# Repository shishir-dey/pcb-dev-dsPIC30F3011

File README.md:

# pcb-dev-dsPIC30F3011

<h3>Front View (3D)</h3>

<h3>Bare PCB</h3>

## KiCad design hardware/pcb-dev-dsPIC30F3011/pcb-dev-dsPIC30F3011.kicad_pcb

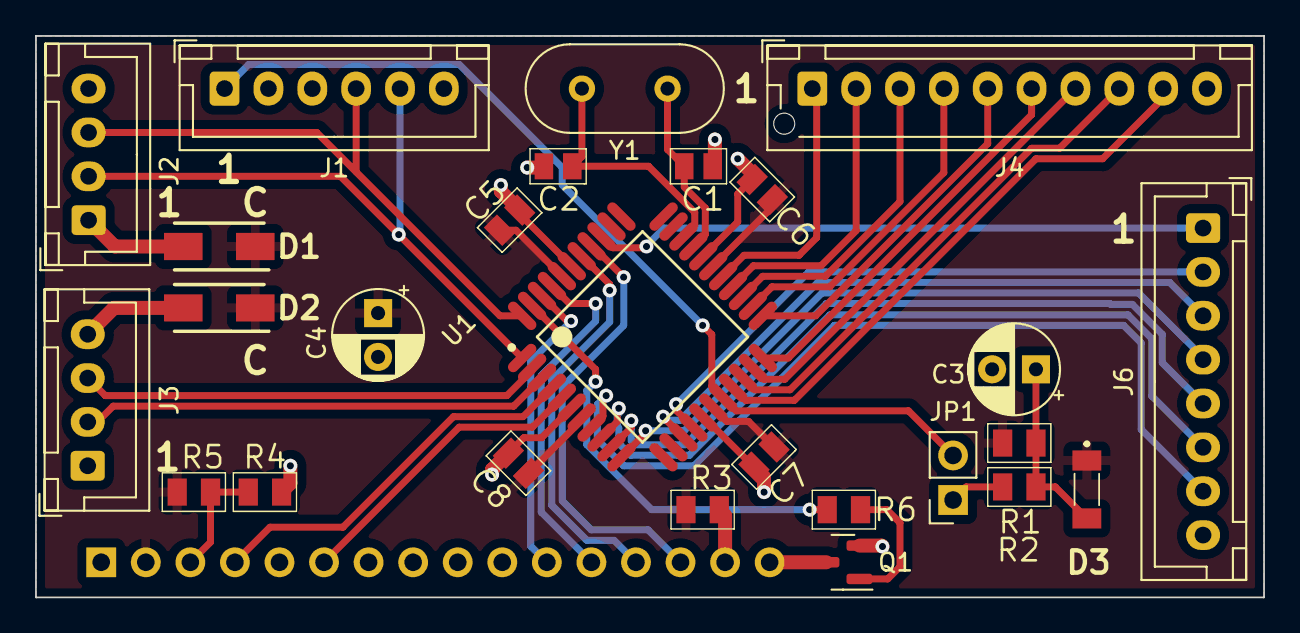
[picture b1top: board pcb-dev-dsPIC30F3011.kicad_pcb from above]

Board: 2 copper layers, 70.0 x 32.0 mm, 27 parts (1 on the bottom side), 40 nets.

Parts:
C1, C2: 22pf, 0805; CAPC2012X90N
C3: 2.2uF, 25V; CP_Radial_D5.0mm_P2.50mm
C4: 10nF, 63V; CP_Radial_D5.0mm_P2.50mm
C5, C6, C7, C8: 104, 0805; CAPC2012X90N
D1, D2: D; DIOM5127X229N
D3: CLL4148; FDLL4448
J1: Conn_PIC_ICSP_ICD; JST_XH_B6B-XH-A_1x06_P2.50mm_Vertical
J2, J3: 4 pin JST 2.54; JST_XH_B4B-XH-A_1x04_P2.50mm_Vertical
J4: 10 pin JST 2.54; JST_XH_B10B-XH-AM_1x10_P2.50mm_Vertical
J5: 16 pin header 2.54; PinSocket_1x16_P2.54mm_Vertical
J6: 8 pin JST 2.54; JST_XH_B8B-XH-A_1x08_P2.50mm_Vertical
JP1: Jumper; PinSocket_1x02_P2.54mm_Vertical
Q1: BC847, SOT-23; SOT-23
R1: 22K,0805; RESC2012X60N
R2: 470E,0805; RESC2012X60N
R3: SHORT; RESC2012X60N
R4: 1K; RESC2012X60N
R5: 9.1K; RESC2012X60N
R6: 22E; RESC2012X60N
U1: DSPIC30F3011-30I_PT; Microchip-DSPIC30F3011-30I_PT-Level_A
Y1: Crystal; Crystal_HC49-U_Vertical

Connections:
+5V: C4.1, C5.1, C6.1, C7.1, C8.1, D1.1 (K), D2.1 (K), D3.1 (K), J5.2, R1.1, R3.1, R5.2, U1.7 (VDD), U1.17 (AVDD), U1.28 (VDD), U1.40 (VDD)
ADC0: J4.9, U1.19 (EMUD3/AN0/VREF+/CN2/RB0)
ADC1: J4.8, U1.20 (EMUC3/AN1/VREF-/CN3/RB1)
ADC2: J4.7, U1.21 (~SS1/CN4RB2)
ADC3: J4.6, U1.22 (AN3/INDX/CN5/RB3)
ADC4: J4.5, U1.23 (AN4/QEA/IC7/CN6/RB4)
ADC5: J4.4, U1.24 (AN5/QEB/IC8/CN7/RB5)
ADC6: J4.3, U1.25 (AN6/OCFA/RB6)
ADC7: J4.2, U1.26 (AN7/RB7)
ADC8: J4.1, U1.27 (AN8/RB8)
CLKIN: C1.1, U1.30 (OSC1/CLKI), Y1.1
CLKOUT: C2.1, U1.31 (OSC2/CLKO/RC15), Y1.2
FAULT: J6.1, U1.36 (~FLTA/INT0RE8)
GND: C1.2, C2.2, C3.2, C4.2, C5.2, C6.2, C7.2, C8.2, J1.3 (VSS), J2.4, J3.1, J4.10, J5.1, J5.5, J5.7, J5.8, J5.9, J5.10, J6.8, Q1.2 (E), R4.1, U1.6 (VSS), U1.16 (AVSS), U1.29 (VSS), U1.39 (VSS)
LCD_BACKLIGHT: R6.1, U1.43 (SCK1/RF6)
LCD_CS_RS: J5.4, U1.4 (RF1)
LCD_DATA0: J5.11, U1.42 (EMUC2/OC1/IC1/INT1/RD0)
LCD_DATA1: J5.12, U1.41 (OC3/RD2)
LCD_DATA2: J5.13, U1.38 (OC4/RD3)
LCD_DATA3: J5.14, U1.37 (EMUD2/OC2/IC2/INT2/RD1)
LCD_WR_ENABLE: J5.6, U1.5 (RF0)
unnamed: C3.1, D3.2 (A), R1.2, R2.2
unnamed: J5.3, R4.2, R5.1
unnamed: J5.15, R3.2
unnamed: J5.16, Q1.3 (C)
unnamed: JP1.1 (A), R2.1
unnamed: Q1.1 (B), R6.2
PICkit4_MCLR: J1.1 (~MCLR/VPP), JP1.2 (B), U1.18 (~MCLR)
PICkit4_PGC: J1.5 (PGC/ICSPCLK), J2.2, U1.1 (PGC/EMUC/U1RX/SDI1/SDA/RF2)
PICkit4_PGD: J1.4 (PGD/ICSPDAT), J2.3, U1.44 (PGD/EMUD/U1TX/SDO1/SCL/RF3)
PWM1H: J6.3, U1.14 (PWM1H/RE1)
PWM1L: J6.2, U1.15 (PWM1L/RE0)
PWM2H: J6.5, U1.10 (PWM2H/RE3)
PWM2L: J6.4, U1.11 (PWM2L/RE2)
PWM3H: J6.7, U1.8 (PWM3H/RE5)
PWM3L: J6.6, U1.9 (PWM3L/RE4)
UART1_+5V: D1.2 (A), J2.1
UART2_+5V: D2.2 (A), J3.4
UART2_RX: J3.2, U1.3 (U2RX/CN17/RF4)
UART2_TX: J3.3, U1.2 (U2TX/CN18/RF5)

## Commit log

2022-06-13 Add schematics and layout
2022-06-13 Add interactive BOM
2024-04-16 Move the link to GitHub Pages from the README to the About section
